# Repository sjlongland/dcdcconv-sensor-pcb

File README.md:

[Find this project on codeberg](https://codeberg.org/sjlongland/dcdcconv-sensor-pcb)

As a result of Github's decision to force AI-generated issues with no opt-out,
I am migrating personal projects of mine to Codeberg.  The project at Github
will be archived.

----

# Voltage/Current sensor board

This is a differential I²C voltage and current sensing board using the TI
INA219 power monitor IC and the NXP PCA9615 differential I²C controller.  This
is intended to provide a high-accuracy voltage and current measurement for the
[DC-DC converter
controller](https://codeberg.org/sjlongland/dcdcconv-controller-pcb).

There is a footprint for an on-board current shunt (e.g. TT Electronics
LRMAP5930B-R0002FT) as well as a connector for an off-board one.  The board
also has footprints for two screw terminal blocks (Phoenix Contact "Combicon"
1706785) to interface the board to up to 6AWG cables for power input/output.

Four two-way jumpers allow full freedom in selecting the I²C address used by
the INA219 according to combinations of settings chosen from its data sheet.

The underside has exposed copper areas to allow additional stranded cable to
be soldered over the traces to enhance the current carrying capability.

## Parts list

* C1, C3: 100nF ≥10V ceramic capacitor 0805 SMD (localised decoupling)
* C2: ≥100µF ≥10V electrolytic capacitor 6.3mm SMD (bulk decoupling)
* (**FIT ONE ONLY**) C4, C5, C6, C7: 100pF ≥20V ceramic capacitor (0V AC
  decoupling capacitor to chassis.  Choose the capacitor that best suits your
  mounting arrangements.)
* U1: NXP PCA9615 differential I²C controller.
* U2: TI INA219BIDR power monitor.
* R1, R6: (**NOT CONFIRMED**) 2k2 ohm 0805 SMD resistors (differential I²C
  pull-up)
* R4, R9: Spaces for additional pull-ups for differential I²C, do not fit
  unless found to be required.
* R5, R10: (**NOT CONFIRMED**) 2k2 ohm 0805 SMD resistors (differential I²C
  pull-down)
* R2, R7: Spaces for additional pull-downs for differential I²C, do not fit
  unless found to be required.
* R3, R8: (**NOT CONFIRMED**) 100 ohm 0805 SMD resistors (differential I²C
  termination)
* R12, R13: (**NOT CONFIRMED**) 2k2 ohm 0805 SMD resistors (I²C pull-up)
* J1: 6-pin 2.54mm "KK" connector (differential I²C bus)
* J2: 2-pin 2.54mm "KK" connector (external current shunt, **omit if fitting
  R11)

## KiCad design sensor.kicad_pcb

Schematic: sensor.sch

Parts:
C1, C3: 100n; C_0805_2012Metric_Pad1.15x1.40mm_HandSolder
C2: 100u; CP_Elec_6.3x9.9
C4, C5, C6, C7: 100p; C_0805_2012Metric_Pad1.15x1.40mm_HandSolder
J1: CTRL; Molex_KK-254_AE-6410-06A_1x06_P2.54mm_Vertical
J2: Conn_01x04; PinHeader_1x04_P2.54mm_Vertical
JP1, JP3, JP4: SolderJumper_3_Open; SolderJumper-3_P1.3mm_Open_RoundedPad1.0x1.5mm
JP2: SolderJumper_3_Bridged12; SolderJumper-3_P1.3mm_Bridged12_RoundedPad1.0x1.5mm
MH1, MH2, MH3, MH4: MountingHole_Pad; MountingHole_3.2mm_M3_Pad_Via
R1, R2, R4, R5, R6, R7, R9, R10, R12, R13: 2k2; R_0805_2012Metric_Pad1.15x1.40mm_HandSolder
R3, R8: 100R; R_0805_2012Metric_Pad1.15x1.40mm_HandSolder
U1: PCA9615; TSSOP-10_3x3mm_P0.5mm
U2: INA219BIDR; SOIC-8_3.9x4.9mm_P1.27mm

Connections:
/A0: JP3.2, JP4.2, U2.2 (A0)
/A1: JP1.2, JP2.2, U2.1 (A1)
/SCL: JP1.1, JP3.1, R13.2, U1.4, U2.4 (SCL)
/SCL+: J1.5, R6.2, R7.1, R8.1, U1.7
/SCL-: J1.6, R8.2, R9.2, R10.1, U1.6
/SDA: JP1.3, JP3.3, R12.2, U1.2, U2.3 (SDA)
/SDA+: J1.3, R1.2, R2.1, R3.1, U1.8
/SDA-: J1.4, R3.2, R4.2, R5.1, U1.9
/SHUNT+: J2.2, U2.8 (IN+)
/SHUNT-: J2.3, U2.7 (IN–)
GND: C1.2, C2.2, C3.2, C4.2, C5.2, C6.2, C7.2, J1.2, J2.1, J2.4, JP2.1, JP4.1, R2.2, R5.2, R7.2, R10.2, U1.5, U2.6 (GND)
unnamed: C4.1, MH1.1
unnamed: C5.1, MH2.1
unnamed: C6.1, MH3.1
unnamed: C7.1, MH4.1
VCC: C1.1, C2.1, C3.1, J1.1, JP2.3, JP4.3, R1.1, R4.1, R6.1, R9.1, R12.1, R13.1, U1.1, U1.3, U1.10, U2.5 (VS)

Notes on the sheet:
I²C Address selection

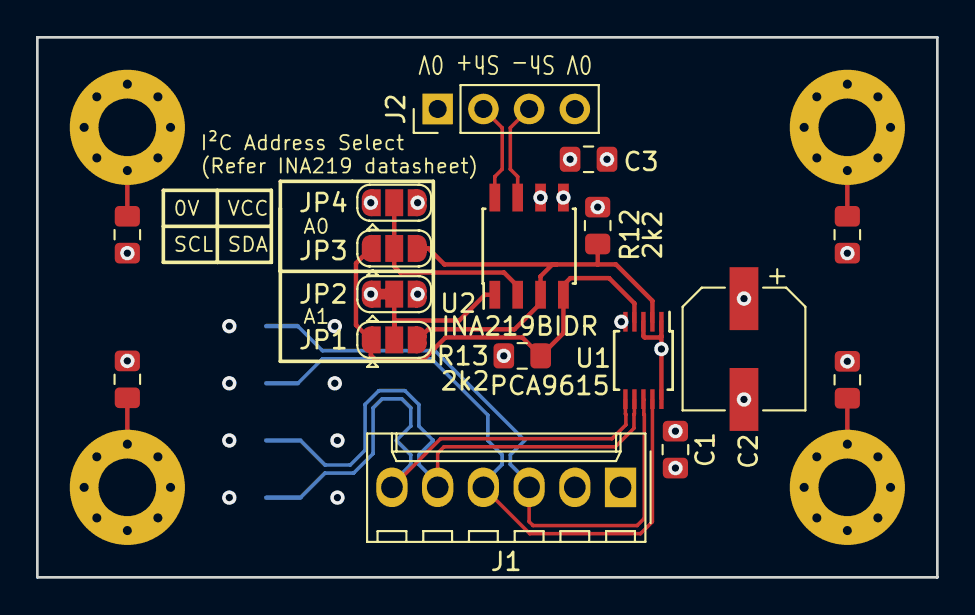
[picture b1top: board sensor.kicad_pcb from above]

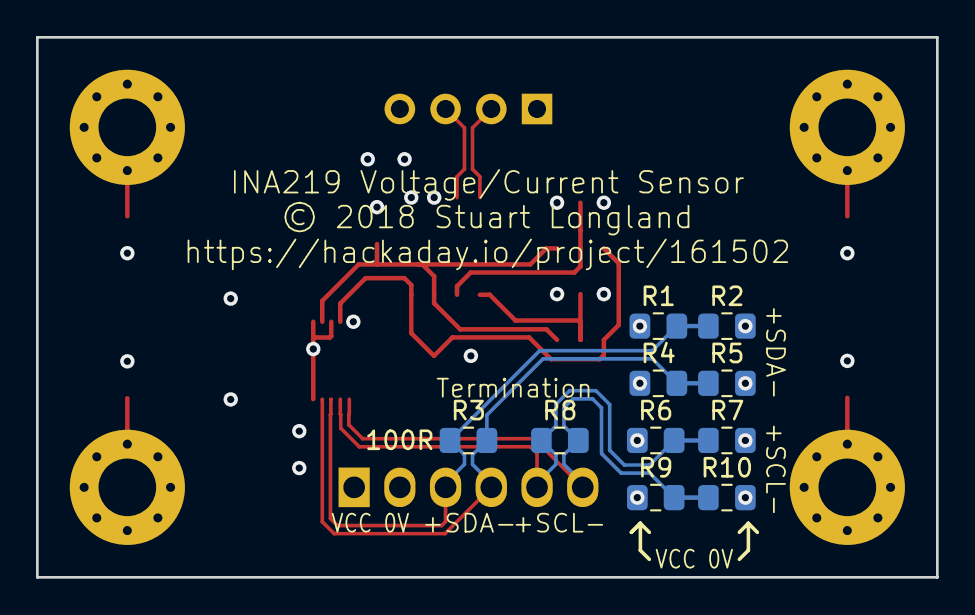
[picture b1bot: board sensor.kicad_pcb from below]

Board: 4 copper layers, 50.0 x 30.0 mm, 31 parts (10 on the bottom side), 16 nets.

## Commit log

2018-10-22 pcb, sch: Drop screw terminals, current shunt.
2018-10-22 gerber: Add CAM production files.
2025-05-30 README.md: update regarding move of project

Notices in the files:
sensor.kicad_pcb:
© 2018 Stuart Longland
